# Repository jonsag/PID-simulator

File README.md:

# PID-simulator
A simulator for students to better understand PID-regulation

## Links

[https://docs.cirkitdesigner.com/component/72ca542f-9daa-409a-9db7-2735e4f8f9b2/n20-motor-with-encoder](https://docs.cirkitdesigner.com/component/72ca542f-9daa-409a-9db7-2735e4f8f9b2/n20-motor-with-encoder)

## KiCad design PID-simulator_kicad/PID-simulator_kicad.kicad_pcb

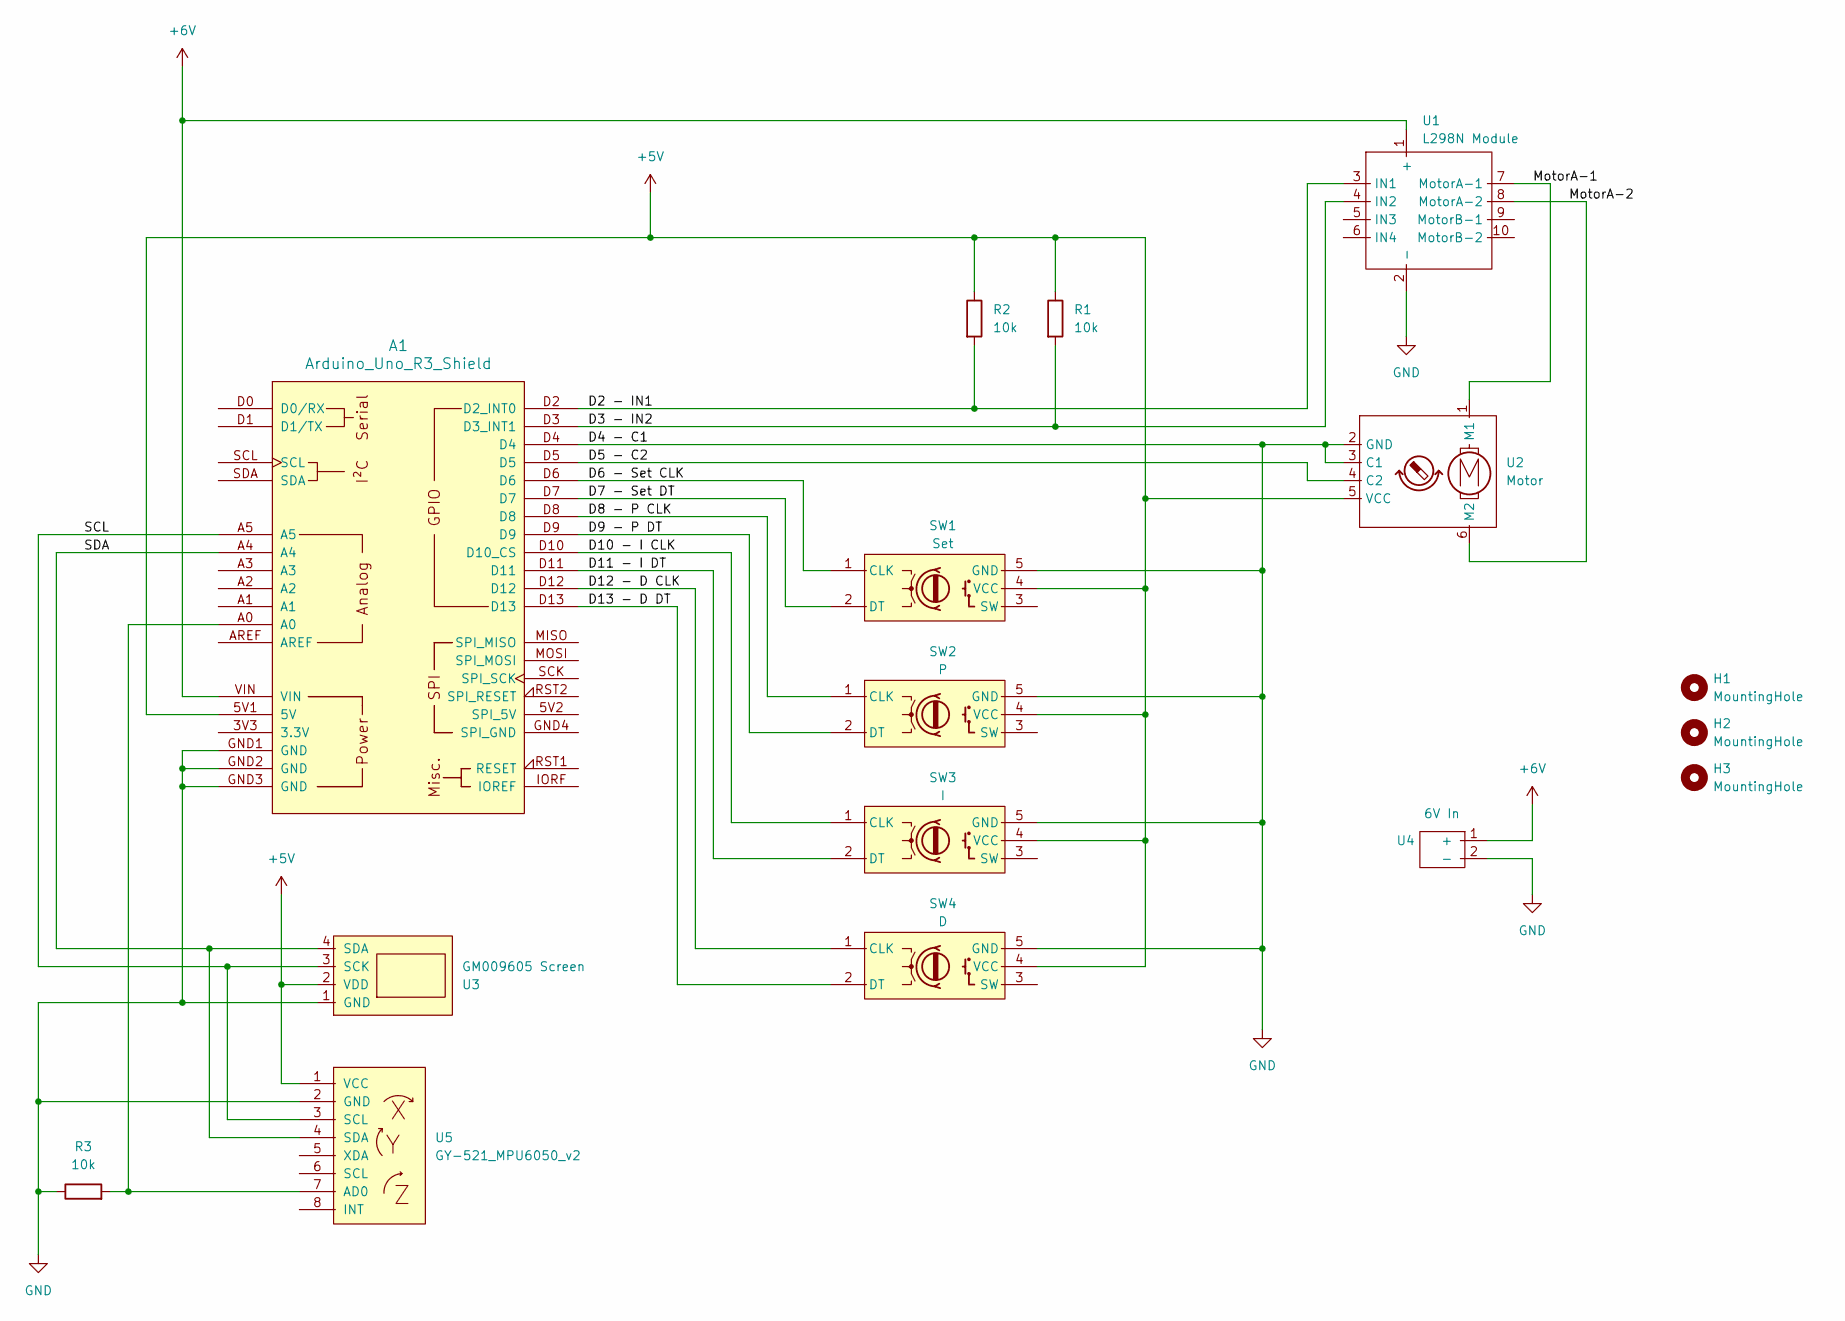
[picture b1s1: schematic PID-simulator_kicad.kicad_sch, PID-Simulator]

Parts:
A1: Arduino_Uno_R3_Shield
H1, H2, H3: MountingHole; MountingHole_3.2mm_M3
R1, R2, R3: 10k; R_Axial_DIN0207_L6.3mm_D2.5mm_P10.16mm_Horizontal
SW1: Set; KY-040_rotary_encoder module_w_header_large
SW2: P; KY-040_rotary_encoder module_w_header_large
SW3: I; KY-040_rotary_encoder module_w_header_large
SW4: D; KY-040_rotary_encoder module_w_header_large
U1: L298N Module; MX1508 - L298N Dual H-Bridge Motor Driver Mini Module
U2: Motor; 6-pin JST N20 DC Motor w Encoder
U3: GM009605 Screen; SSD1306_I2C_0.96_OLED_display_large
U4: 6V In; 2-pole_power_in_screw_terminal
U5: GY-521_MPU6050_v2; 8-pin JST MPU6050

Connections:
+5V: A1.5V1 (5V), R1.1, R2.1, SW1.4 (VCC), SW2.4 (VCC), SW3.4 (VCC), SW4.4 (VCC), U2.5 (VCC), U3.2 (VDD), U5.1 (VCC)
+6V: A1.VIN, U1.1 (+), U4.1 (+)
/D2 - IN1: A1.D2 (D2_INT0), R2.2, U1.3 (IN1)
/D3 - IN2: A1.D3 (D3_INT1), R1.2, U1.4 (IN2)
/D5 - C2: A1.D5, U2.4 (C2)
/D6 - Set CLK: A1.D6, SW1.1 (CLK)
/D7 - Set DT: A1.D7, SW1.2 (DT)
/D8 - P CLK: A1.D8, SW2.1 (CLK)
/D9 - P DT: A1.D9, SW2.2 (DT)
/D10 - I CLK: A1.D10 (D10_CS), SW3.1 (CLK)
/D11 - I DT: A1.D11, SW3.2 (DT)
/D12 - D CLK: A1.D12, SW4.1 (CLK)
/D13 - D DT: A1.D13, SW4.2 (DT)
/MotorA-1: U1.7 (MotorA-1), U2.1 (M1)
/MotorA-2: U1.8 (MotorA-2), U2.6 (M2)
/SCL: A1.A5, U3.3 (SCK), U5.3 (SCL)
/SDA: A1.A4, U3.4 (SDA), U5.4 (SDA)
GND: A1.D4, A1.GND1 (GND), A1.GND2 (GND), A1.GND3 (GND), R3.1, SW1.5 (GND), SW2.5 (GND), SW3.5 (GND), SW4.5 (GND), U1.2 (-), U2.2 (GND), U2.3 (C1), U3.1 (GND), U4.2 (-), U5.2 (GND)
unnamed: A1.A0, R3.2, U5.7 (AD0)

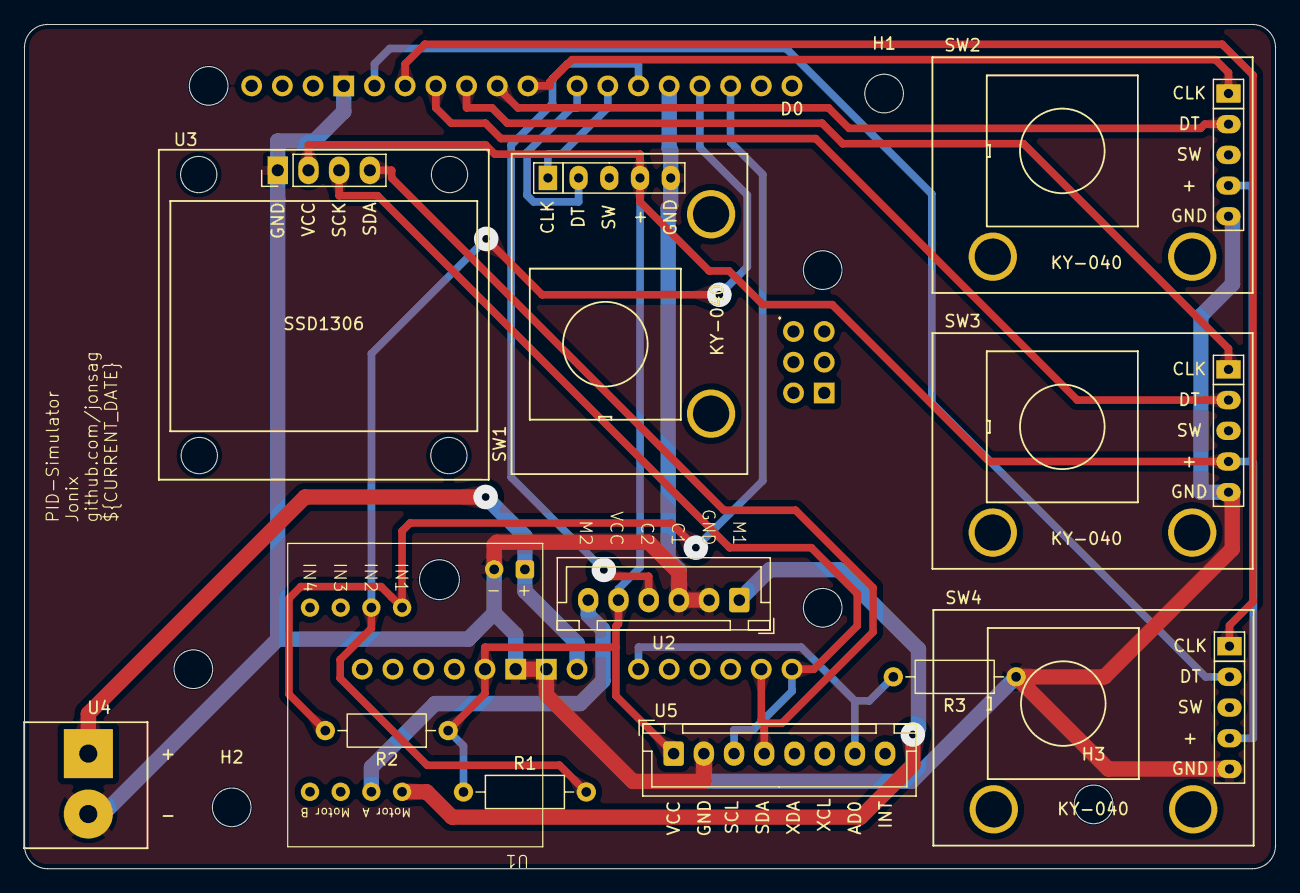
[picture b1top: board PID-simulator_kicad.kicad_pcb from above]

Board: 2 copper layers, 103.5 x 69.9 mm, 16 parts (0 on the bottom side), 19 nets.

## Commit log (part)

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2026-05-16 schematics and pcb
2026-06-04 pcb update
2026-06-05 PIO skeleton
